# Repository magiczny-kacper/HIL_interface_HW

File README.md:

# HIL_interface_HW
Analog and digital I/O shield for Nucleo-144 board, designed for HIL simulation

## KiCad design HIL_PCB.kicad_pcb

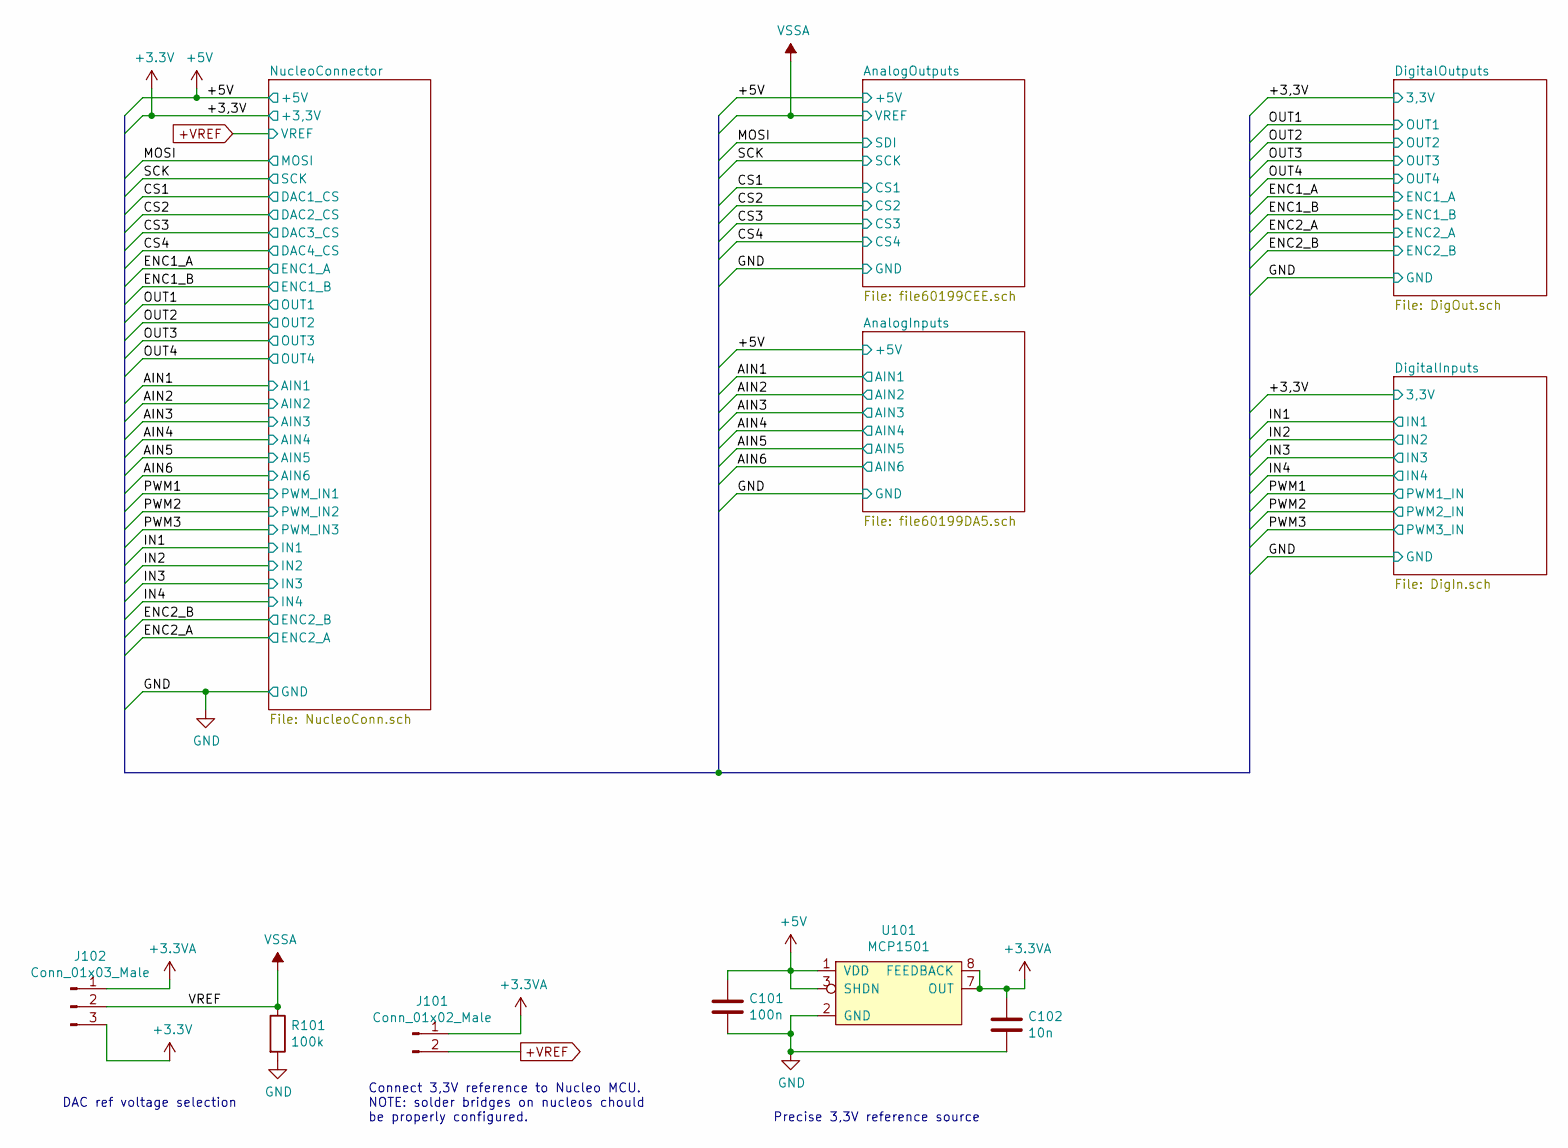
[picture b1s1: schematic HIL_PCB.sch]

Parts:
C101: 100n; C_0805_2012Metric
C102: 10n; C_0805_2012Metric
J101: Conn_01x02_Male; PinHeader_1x02_P2.54mm_Vertical
J102: Conn_01x03_Male; PinHeader_1x03_P2.54mm_Vertical
R101: 100k; R_0805_2012Metric
U101: MCP1501; SOIC-8_3.9x4.9mm_P1.27mm

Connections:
+3.3VA: C102.1, J101.1, J102.1, U101.7 (OUT), U101.8 (FEEDBACK)
+3V3: J102.3; also elsewhere on the board
+5V: C101.1, U101.1 (VDD), U101.3 (SHDN); also elsewhere on the board
+VREF: J101.2; also elsewhere on the board
GND: C101.2, C102.2, R101.2, U101.2 (GND), U101.4 (GND), U101.5 (GND), U101.6 (GND); also elsewhere on the board
VSSA: J102.2, R101.1; also elsewhere on the board

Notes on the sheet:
Connect 3,3V reference to Nucleo MCU. NOTE: solder bridges on nucleos chould be properly configured.
DAC ref voltage selection
Precise 3,3V reference source

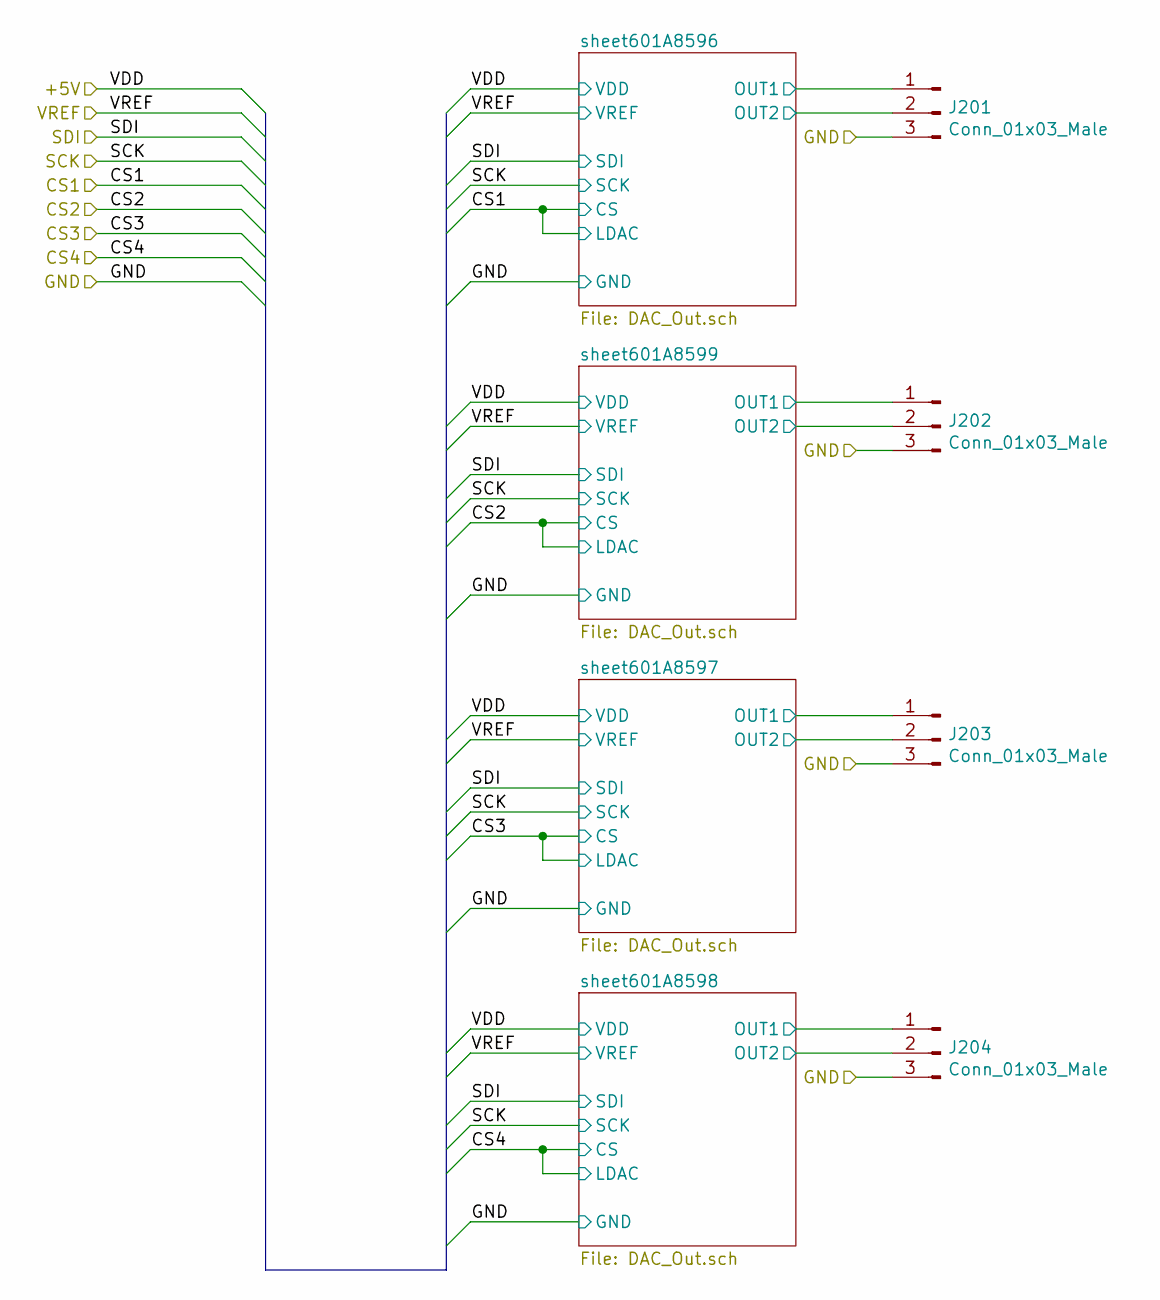
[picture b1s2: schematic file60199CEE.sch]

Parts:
J201, J202, J203, J204: Conn_01x03_Male; PinHeader_1x03_P2.54mm_Vertical

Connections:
/AnalogOutputs/sheet601A8596/OUT1: J201.1; also elsewhere on the board
/AnalogOutputs/sheet601A8596/OUT2: J201.2; also elsewhere on the board
/AnalogOutputs/sheet601A8597/OUT1: J203.1; also elsewhere on the board
/AnalogOutputs/sheet601A8597/OUT2: J203.2; also elsewhere on the board
/AnalogOutputs/sheet601A8598/OUT1: J204.1; also elsewhere on the board
/AnalogOutputs/sheet601A8598/OUT2: J204.2; also elsewhere on the board
/AnalogOutputs/sheet601A8599/OUT1: J202.1; also elsewhere on the board
/AnalogOutputs/sheet601A8599/OUT2: J202.2; also elsewhere on the board
GND: J201.3, J202.3, J203.3, J204.3; also elsewhere on the board

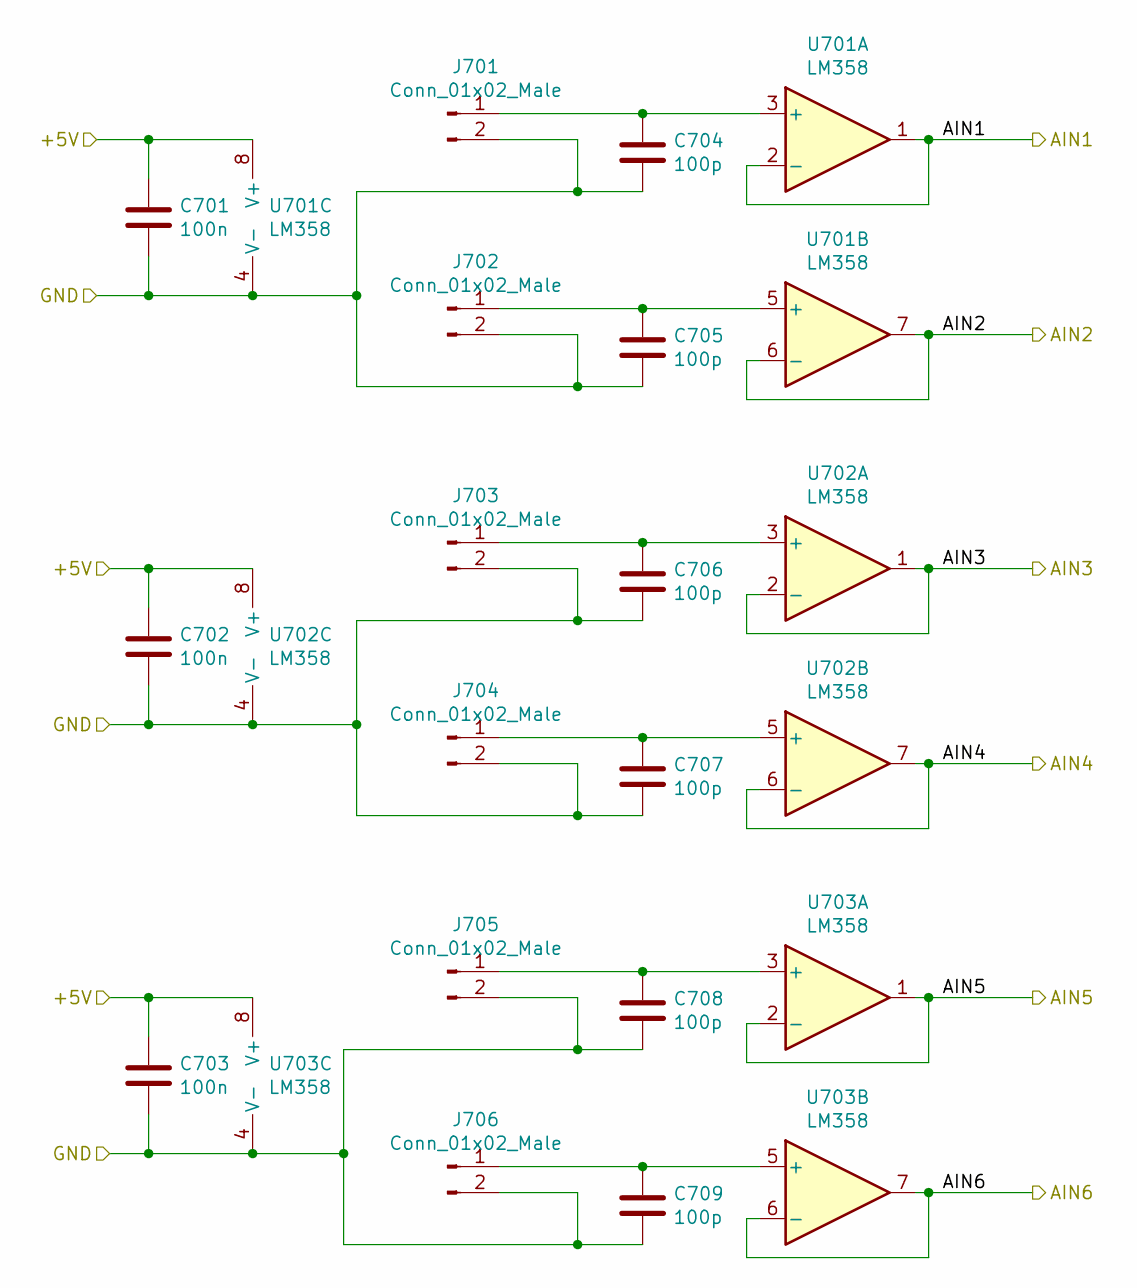
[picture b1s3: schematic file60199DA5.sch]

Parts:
C701, C702, C703: 100n; C_0805_2012Metric
C704, C705, C706, C707, C708, C709: 100p; C_0805_2012Metric
J701, J702, J703, J704, J705, J706: Conn_01x02_Male; PinHeader_1x02_P2.54mm_Vertical
U701, U702, U703: LM358; SO-8_3.9x4.9mm_P1.27mm

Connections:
+5V: C701.1, C702.1, C703.1, U701.8 (V+), U702.8 (V+), U703.8 (V+); also elsewhere on the board
/AIN1: U701.1, U701.2 (-); also elsewhere on the board
/AIN2: U701.6 (-), U701.7; also elsewhere on the board
/AIN3: U702.1, U702.2 (-); also elsewhere on the board
/AIN4: U702.6 (-), U702.7; also elsewhere on the board
/AIN5: U703.1, U703.2 (-); also elsewhere on the board
/AIN6: U703.6 (-), U703.7; also elsewhere on the board
GND: C701.2, C702.2, C703.2, C704.2, C705.2, C706.2, C707.2, C708.2, C709.2, J701.2, J702.2, J703.2, J704.2, J705.2, J706.2, U701.4 (V-), U702.4 (V-), U703.4 (V-); also elsewhere on the board
unnamed: C704.1, J701.1, U701.3 (+)
unnamed: C705.1, J702.1, U701.5 (+)
unnamed: C706.1, J703.1, U702.3 (+)
unnamed: C707.1, J704.1, U702.5 (+)
unnamed: C708.1, J705.1, U703.3 (+)
unnamed: C709.1, J706.1, U703.5 (+)

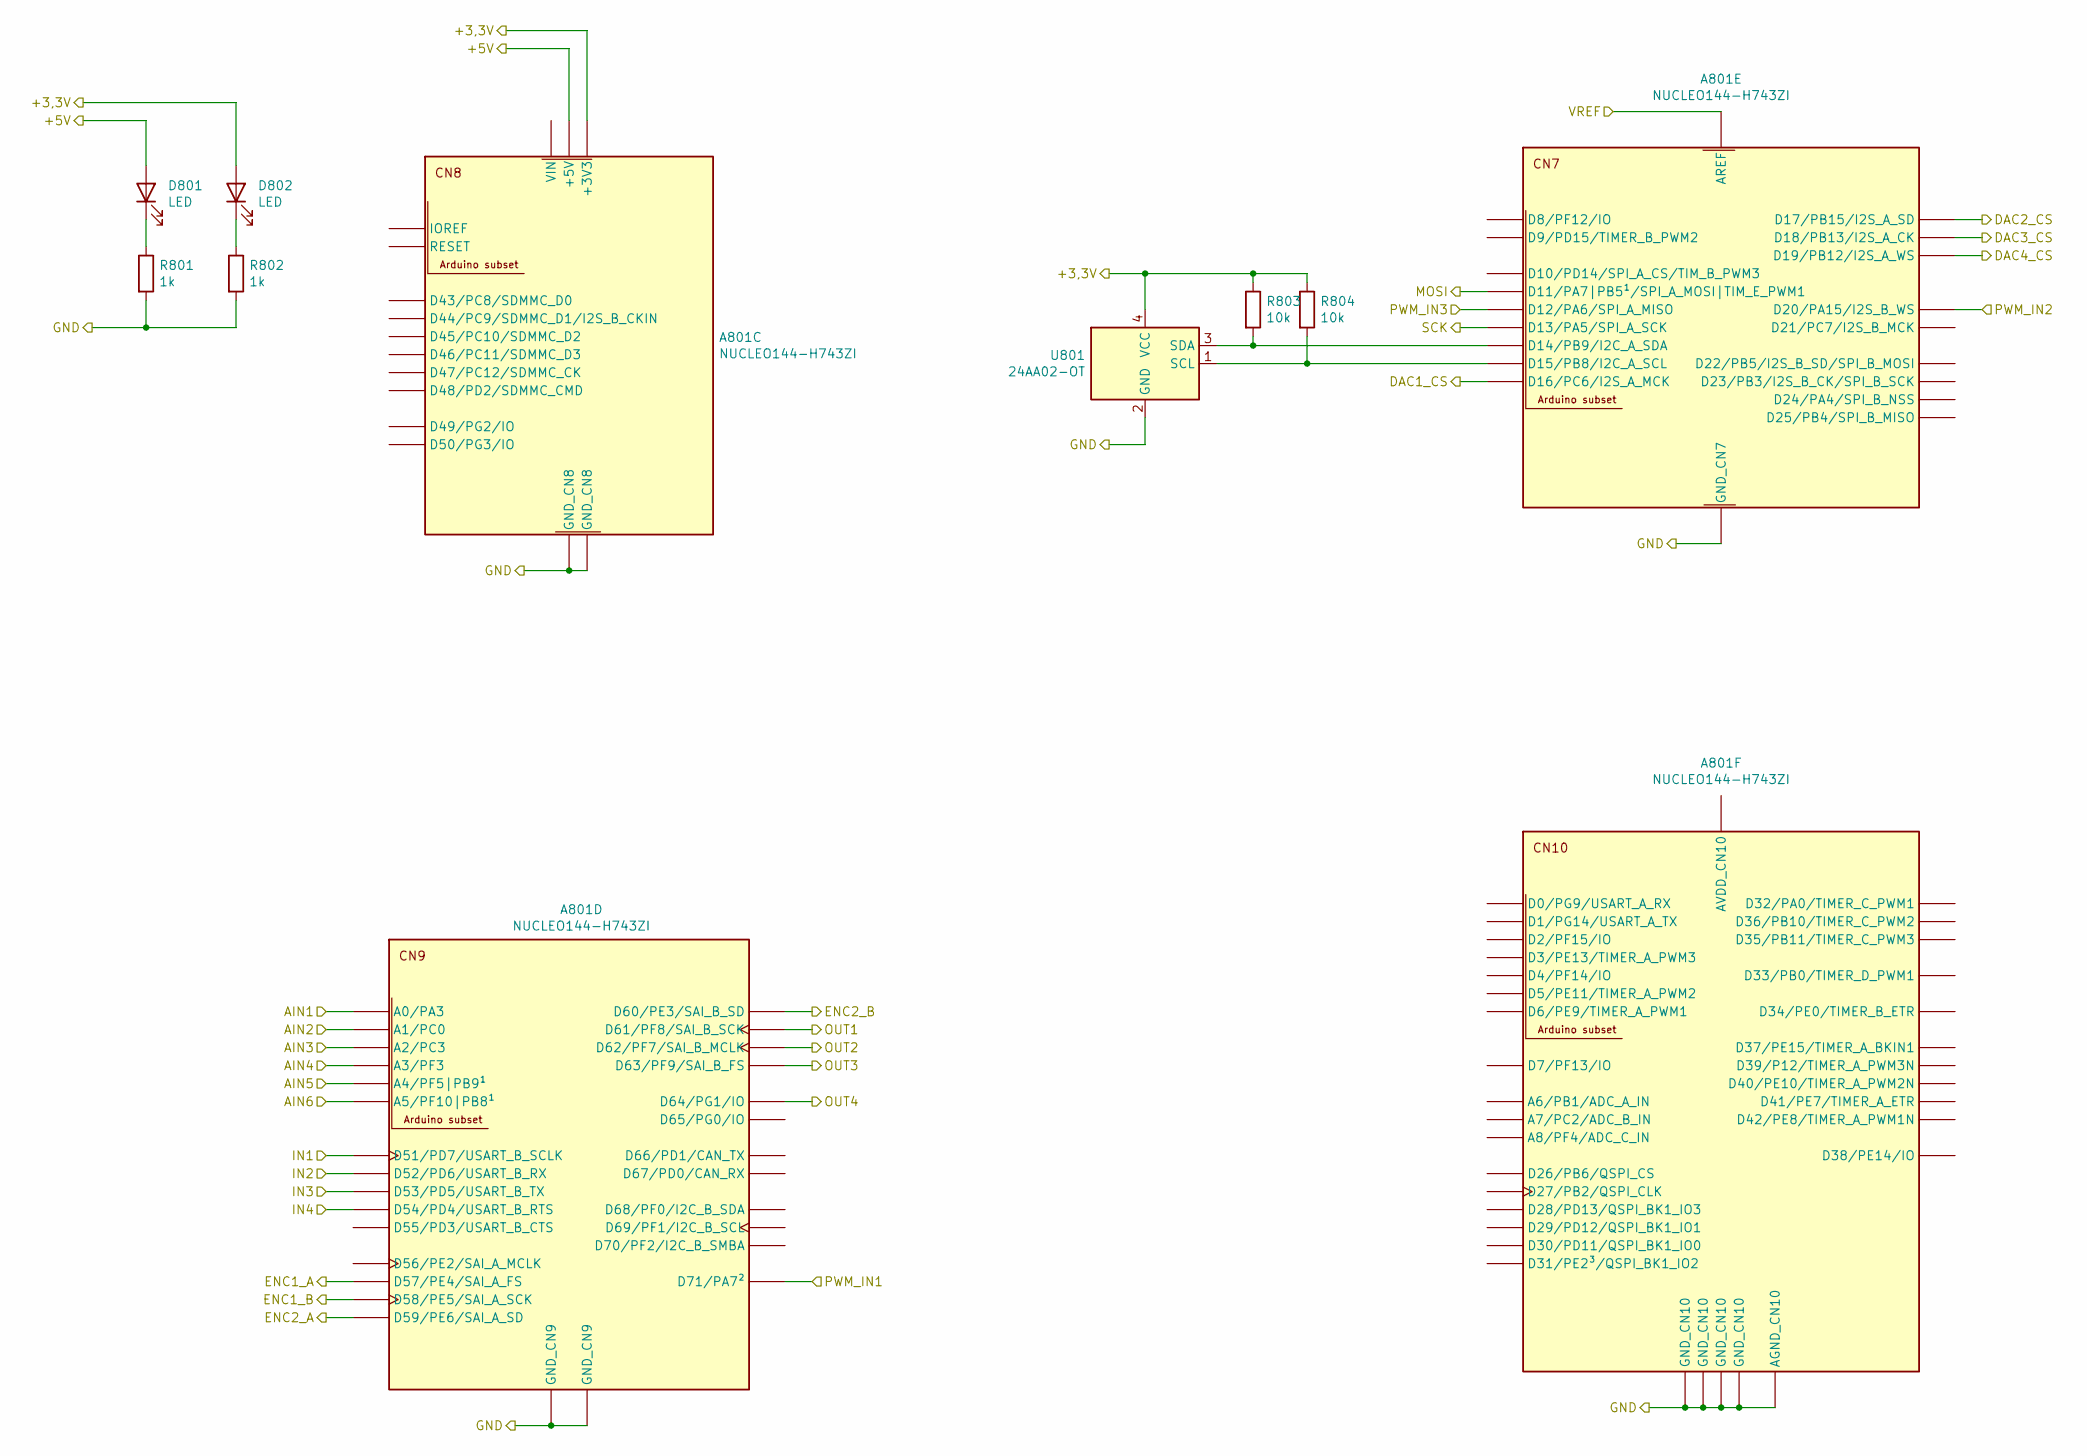
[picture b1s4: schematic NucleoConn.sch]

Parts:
A801: NUCLEO144-H743ZI; ST_Morpho_and_Zio_Connectors_144_STLink
D801, D802: LED; D_0805_2012Metric
R801, R802: 1k; R_0805_2012Metric
R803, R804: 10k; R_0805_2012Metric
U801: 24AA02-OT; SOT-23-5

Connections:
+3V3: A801.CN8_7 (+3V3), D802.2 (A), R803.1, R804.1, U801.4 (VCC); also elsewhere on the board
+5V: A801.CN8_9 (+5V), D801.2 (A); also elsewhere on the board
+VREF: A801.CN7_6 (AREF); also elsewhere on the board
/AIN1: A801.CN9_1 (A0/PA3); also elsewhere on the board
/AIN2: A801.CN9_3 (A1/PC0); also elsewhere on the board
/AIN3: A801.CN9_5 (A2/PC3); also elsewhere on the board
/AIN4: A801.CN9_7 (A3/PF3); also elsewhere on the board
/AIN5: A801.CN9_9 (A4/PF5|PB9¹); also elsewhere on the board
/AIN6: A801.CN9_11 (A5/PF10|PB8¹); also elsewhere on the board
/CS1: A801.CN7_1 (D16/PC6/I2S_A_MCK); also elsewhere on the board
/CS2: A801.CN7_3 (D17/PB15/I2S_A_SD); also elsewhere on the board
/CS3: A801.CN7_5 (D18/PB13/I2S_A_CK); also elsewhere on the board
/CS4: A801.CN7_7 (D19/PB12/I2S_A_WS); also elsewhere on the board
/ENC1_A: A801.CN9_16 (D57/PE4/SAI_A_FS); also elsewhere on the board
/ENC1_B: A801.CN9_18 (D58/PE5/SAI_A_SCK); also elsewhere on the board
/ENC2_A: A801.CN9_20 (D59/PE6/SAI_A_SD); also elsewhere on the board
/ENC2_B: A801.CN9_22 (D60/PE3/SAI_B_SD); also elsewhere on the board
/IN1: A801.CN9_2 (D51/PD7/USART_B_SCLK); also elsewhere on the board
/IN2: A801.CN9_4 (D52/PD6/USART_B_RX); also elsewhere on the board
/IN3: A801.CN9_6 (D53/PD5/USART_B_TX); also elsewhere on the board
/IN4: A801.CN9_8 (D54/PD4/USART_B_RTS); also elsewhere on the board
/MOSI: A801.CN7_14 (D11/PA7|PB5¹/SPI_A_MOSI|TIM_E_PWM1); also elsewhere on the board
/OUT1: A801.CN9_24 (D61/PF8/SAI_B_SCK); also elsewhere on the board
/OUT2: A801.CN9_26 (D62/PF7/SAI_B_MCLK); also elsewhere on the board
/OUT3: A801.CN9_28 (D63/PF9/SAI_B_FS); also elsewhere on the board
/OUT4: A801.CN9_30 (D64/PG1/IO); also elsewhere on the board
/PWM1: A801.CN9_15 (D71/PA7²); also elsewhere on the board
/PWM2: A801.CN7_9 (D20/PA15/I2S_B_WS); also elsewhere on the board
/PWM3: A801.CN7_12 (D12/PA6/SPI_A_MISO); also elsewhere on the board
/SCK: A801.CN7_10 (D13/PA5/SPI_A_SCK); also elsewhere on the board
GND: A801.CN7_8 (GND_CN7), A801.CN8_11 (GND_CN8), A801.CN8_13 (GND_CN8), A801.CN9_12 (GND_CN9), A801.CN9_23 (GND_CN9), A801.CN10_3 (AGND_CN10), A801.CN10_5 (GND_CN10), A801.CN10_17 (GND_CN10), A801.CN10_22 (GND_CN10), A801.CN10_27 (GND_CN10), R801.2, R802.2, U801.2 (GND); also elsewhere on the board
unnamed: A801.CN7_2 (D15/PB8/I2C_A_SCL), R804.2, U801.1 (SCL)
unnamed: A801.CN7_4 (D14/PB9/I2C_A_SDA), R803.2, U801.3 (SDA)
unnamed: D801.1 (K), R801.1
unnamed: D802.1 (K), R802.1

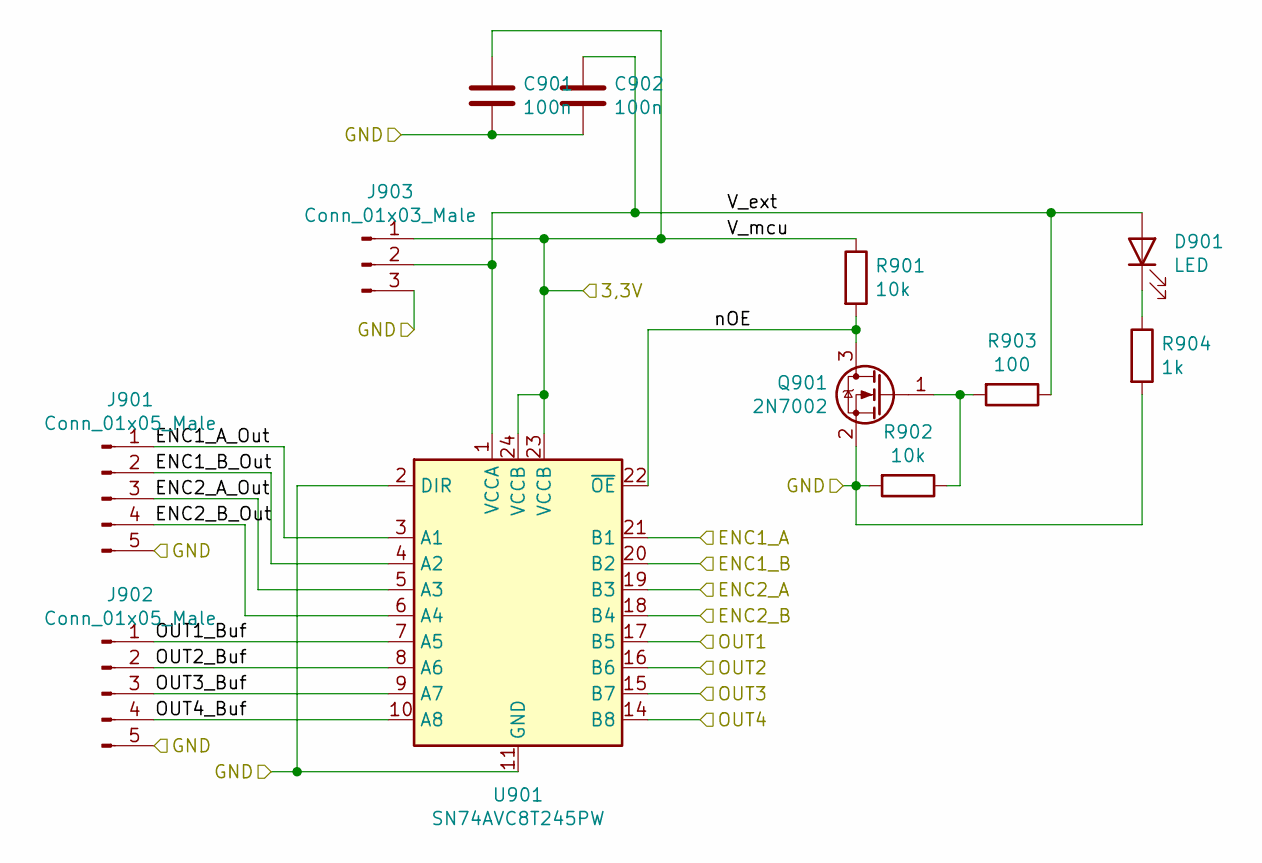
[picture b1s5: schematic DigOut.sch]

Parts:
C901, C902: 100n; C_0805_2012Metric
D901: LED; D_0805_2012Metric
J901, J902: Conn_01x05_Male; PinHeader_1x05_P2.54mm_Vertical
J903: Conn_01x03_Male; PinHeader_1x03_P2.54mm_Vertical
Q901: 2N7002; SOT-23
R901, R902: 10k; R_0805_2012Metric
R903: 100; R_0805_2012Metric
R904: 1k; R_0805_2012Metric
U901: SN74AVC8T245PW; TSSOP-24_4.4x7.8mm_P0.65mm

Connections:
+3V3: C901.1, J903.1, R901.1, U901.23 (VCCB), U901.24 (VCCB); also elsewhere on the board
/DigitalOutputs/ENC1_A_Out: J901.1, U901.3 (A1)
/DigitalOutputs/ENC1_B_Out: J901.2, U901.4 (A2)
/DigitalOutputs/ENC2_A_Out: J901.3, U901.5 (A3)
/DigitalOutputs/ENC2_B_Out: J901.4, U901.6 (A4)
/DigitalOutputs/OUT1_Buf: J902.1, U901.7 (A5)
/DigitalOutputs/OUT2_Buf: J902.2, U901.8 (A6)
/DigitalOutputs/OUT3_Buf: J902.3, U901.9 (A7)
/DigitalOutputs/OUT4_Buf: J902.4, U901.10 (A8)
/DigitalOutputs/V_ext: C902.1, D901.2 (A), J903.2, R903.1, U901.1 (VCCA)
/DigitalOutputs/nOE: Q901.3 (D), R901.2, U901.22 (~OE)
/ENC1_A: U901.21 (B1); also elsewhere on the board
/ENC1_B: U901.20 (B2); also elsewhere on the board
/ENC2_A: U901.19 (B3); also elsewhere on the board
/ENC2_B: U901.18 (B4); also elsewhere on the board
/OUT1: U901.17 (B5); also elsewhere on the board
/OUT2: U901.16 (B6); also elsewhere on the board
/OUT3: U901.15 (B7); also elsewhere on the board
/OUT4: U901.14 (B8); also elsewhere on the board
GND: C901.2, C902.2, J901.5, J902.5, J903.3, Q901.2 (S), R902.2, R904.2, U901.2 (DIR), U901.11 (GND), U901.12 (GND), U901.13 (GND); also elsewhere on the board
unnamed: D901.1 (K), R904.1
unnamed: Q901.1 (G), R902.1, R903.2

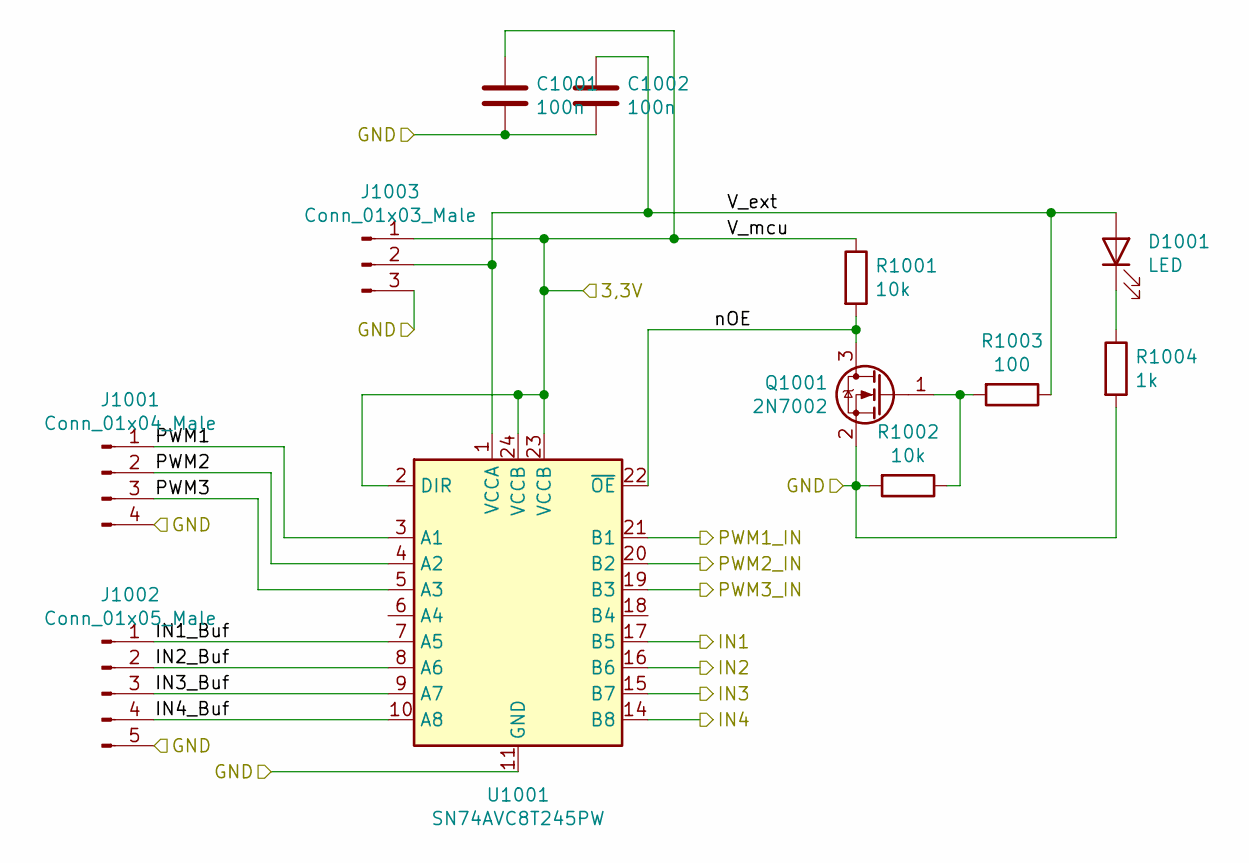
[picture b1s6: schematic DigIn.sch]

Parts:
C1001, C1002: 100n; C_0805_2012Metric
D1001: LED; D_0805_2012Metric
J1001: Conn_01x04_Male; PinHeader_1x04_P2.54mm_Vertical
J1002: Conn_01x05_Male; PinHeader_1x05_P2.54mm_Vertical
J1003: Conn_01x03_Male; PinHeader_1x03_P2.54mm_Vertical
Q1001: 2N7002; SOT-23
R1001, R1002: 10k; R_0805_2012Metric
R1003: 100; R_0805_2012Metric
R1004: 1k; R_0805_2012Metric
U1001: SN74AVC8T245PW; TSSOP-24_4.4x7.8mm_P0.65mm

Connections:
+3V3: C1001.1, J1003.1, R1001.1, U1001.2 (DIR), U1001.23 (VCCB), U1001.24 (VCCB); also elsewhere on the board
/DigitalInputs/IN1_Buf: J1002.1, U1001.7 (A5)
/DigitalInputs/IN2_Buf: J1002.2, U1001.8 (A6)
/DigitalInputs/IN3_Buf: J1002.3, U1001.9 (A7)
/DigitalInputs/IN4_Buf: J1002.4, U1001.10 (A8)
/DigitalInputs/PWM1: J1001.1, U1001.3 (A1)
/DigitalInputs/PWM2: J1001.2, U1001.4 (A2)
/DigitalInputs/PWM3: J1001.3, U1001.5 (A3)
/DigitalInputs/V_ext: C1002.1, D1001.2 (A), J1003.2, R1003.1, U1001.1 (VCCA)
/DigitalInputs/nOE: Q1001.3 (D), R1001.2, U1001.22 (~OE)
/IN1: U1001.17 (B5); also elsewhere on the board
/IN2: U1001.16 (B6); also elsewhere on the board
/IN3: U1001.15 (B7); also elsewhere on the board
/IN4: U1001.14 (B8); also elsewhere on the board
/PWM1: U1001.21 (B1); also elsewhere on the board
/PWM2: U1001.20 (B2); also elsewhere on the board
/PWM3: U1001.19 (B3); also elsewhere on the board
GND: C1001.2, C1002.2, J1001.4, J1002.5, J1003.3, Q1001.2 (S), R1002.2, R1004.2, U1001.11 (GND), U1001.12 (GND), U1001.13 (GND); also elsewhere on the board
unnamed: D1001.1 (K), R1004.1
unnamed: Q1001.1 (G), R1002.1, R1003.2

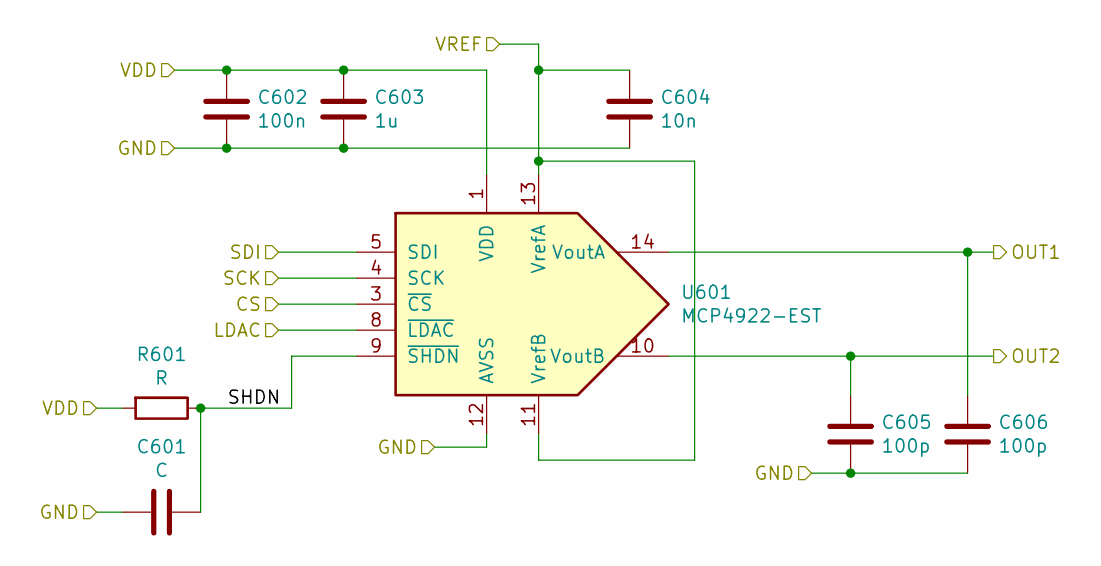
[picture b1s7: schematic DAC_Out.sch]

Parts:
C201: C; C_0805_2012Metric
C202: 100n; C_0805_2012Metric
C203: 1u; C_0805_2012Metric
C204: 10n; C_0805_2012Metric
C205, C206: 100p; C_0805_2012Metric
R201: R; R_0805_2012Metric
U201: MCP4922-EST; TSSOP-14_4.4x5mm_P0.65mm

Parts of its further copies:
C301, C401, C501, C601: C; C_0805_2012Metric
C302, C402, C502, C602: 100n; C_0805_2012Metric
C303, C403, C503, C603: 1u; C_0805_2012Metric
C304, C404, C504, C604: 10n; C_0805_2012Metric
C305, C306, C405, C406, C505, C506, C605, C606: 100p; C_0805_2012Metric
R301, R401, R501, R601: R; R_0805_2012Metric
U301, U401, U501, U601: MCP4922-EST; TSSOP-14_4.4x5mm_P0.65mm

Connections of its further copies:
+5V: C302.1, C303.1, C402.1, C403.1, C502.1, C503.1, C602.1, C603.1, R301.2, R401.2, R501.2, R601.2, U301.1 (VDD), U401.1 (VDD), U501.1 (VDD), U601.1 (VDD); also elsewhere on the board
/AnalogOutputs/sheet601A8596/OUT1: C306.1, U301.14 (VoutA); also elsewhere on the board
/AnalogOutputs/sheet601A8596/OUT2: C305.1, U301.10 (VoutB); also elsewhere on the board
/AnalogOutputs/sheet601A8596/SHDN: C301.1, R301.1, U301.9 (~SHDN~)
/AnalogOutputs/sheet601A8597/OUT1: C406.1, U401.14 (VoutA); also elsewhere on the board
/AnalogOutputs/sheet601A8597/OUT2: C405.1, U401.10 (VoutB); also elsewhere on the board
/AnalogOutputs/sheet601A8597/SHDN: C401.1, R401.1, U401.9 (~SHDN~)
/AnalogOutputs/sheet601A8598/OUT1: C506.1, U501.14 (VoutA); also elsewhere on the board
/AnalogOutputs/sheet601A8598/OUT2: C505.1, U501.10 (VoutB); also elsewhere on the board
/AnalogOutputs/sheet601A8598/SHDN: C501.1, R501.1, U501.9 (~SHDN~)
/AnalogOutputs/sheet601A8599/OUT1: C606.1, U601.14 (VoutA); also elsewhere on the board
/AnalogOutputs/sheet601A8599/OUT2: C605.1, U601.10 (VoutB); also elsewhere on the board
/AnalogOutputs/sheet601A8599/SHDN: C601.1, R601.1, U601.9 (~SHDN~)
/CS1: U301.3 (~CS~), U301.8 (~LDAC~); also elsewhere on the board
/CS2: U601.3 (~CS~), U601.8 (~LDAC~); also elsewhere on the board
/CS3: U401.3 (~CS~), U401.8 (~LDAC~); also elsewhere on the board
/CS4: U501.3 (~CS~), U501.8 (~LDAC~); also elsewhere on the board
/MOSI: U301.5 (SDI), U401.5 (SDI), U501.5 (SDI), U601.5 (SDI); also elsewhere on the board
/SCK: U301.4 (SCK), U401.4 (SCK), U501.4 (SCK), U601.4 (SCK); also elsewhere on the board
GND: C301.2, C302.2, C303.2, C304.2, C305.2, C306.2, C401.2, C402.2, C403.2, C404.2, C405.2, C406.2, C501.2, C502.2, C503.2, C504.2, C505.2, C506.2, C601.2, C602.2, C603.2, C604.2, C605.2, C606.2, U301.12 (AVSS), U401.12 (AVSS), U501.12 (AVSS), U601.12 (AVSS); also elsewhere on the board
VSSA: C304.1, C404.1, C504.1, C604.1, U301.11 (VrefB), U301.13 (VrefA), U401.11 (VrefB), U401.13 (VrefA), U501.11 (VrefB), U501.13 (VrefA), U601.11 (VrefB), U601.13 (VrefA); also elsewhere on the board

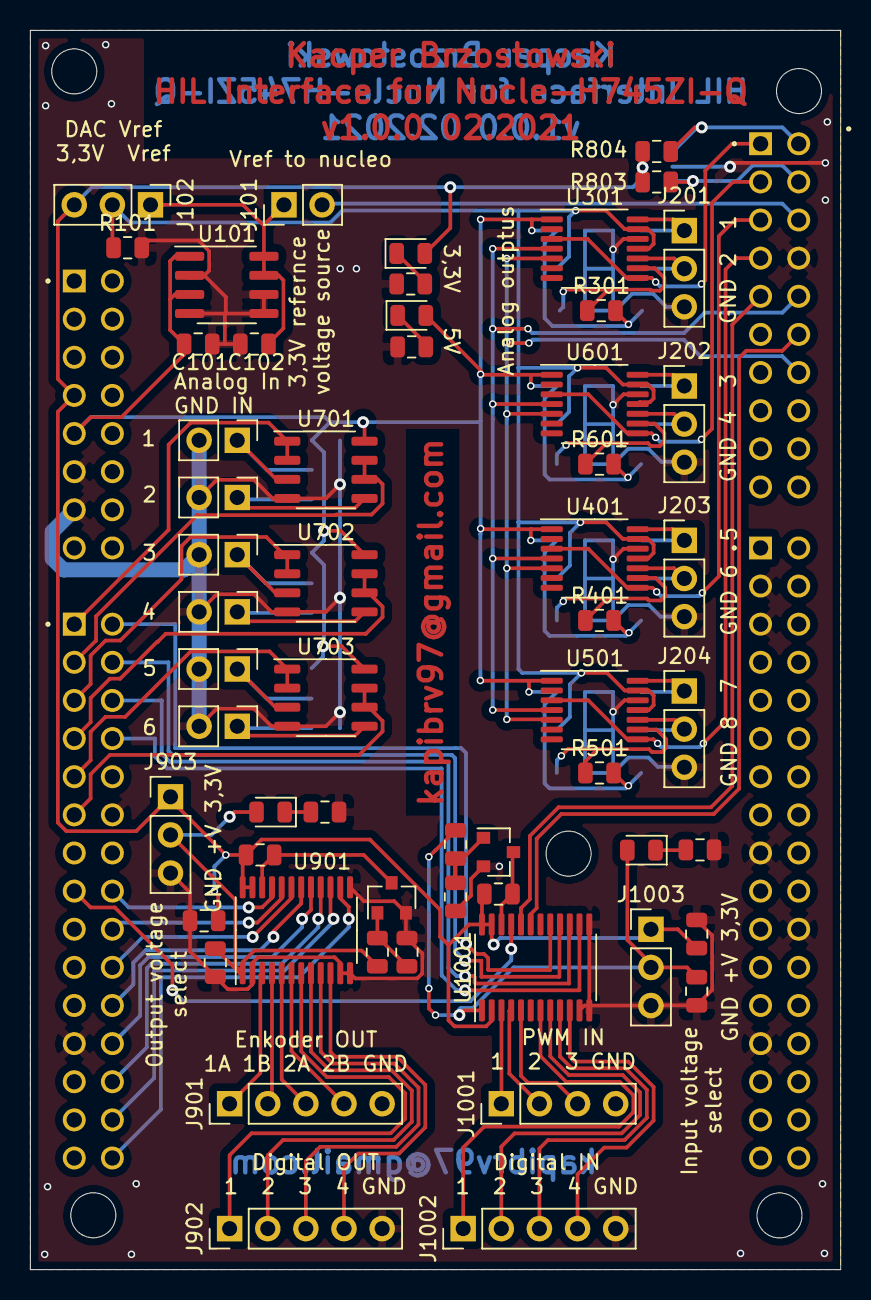
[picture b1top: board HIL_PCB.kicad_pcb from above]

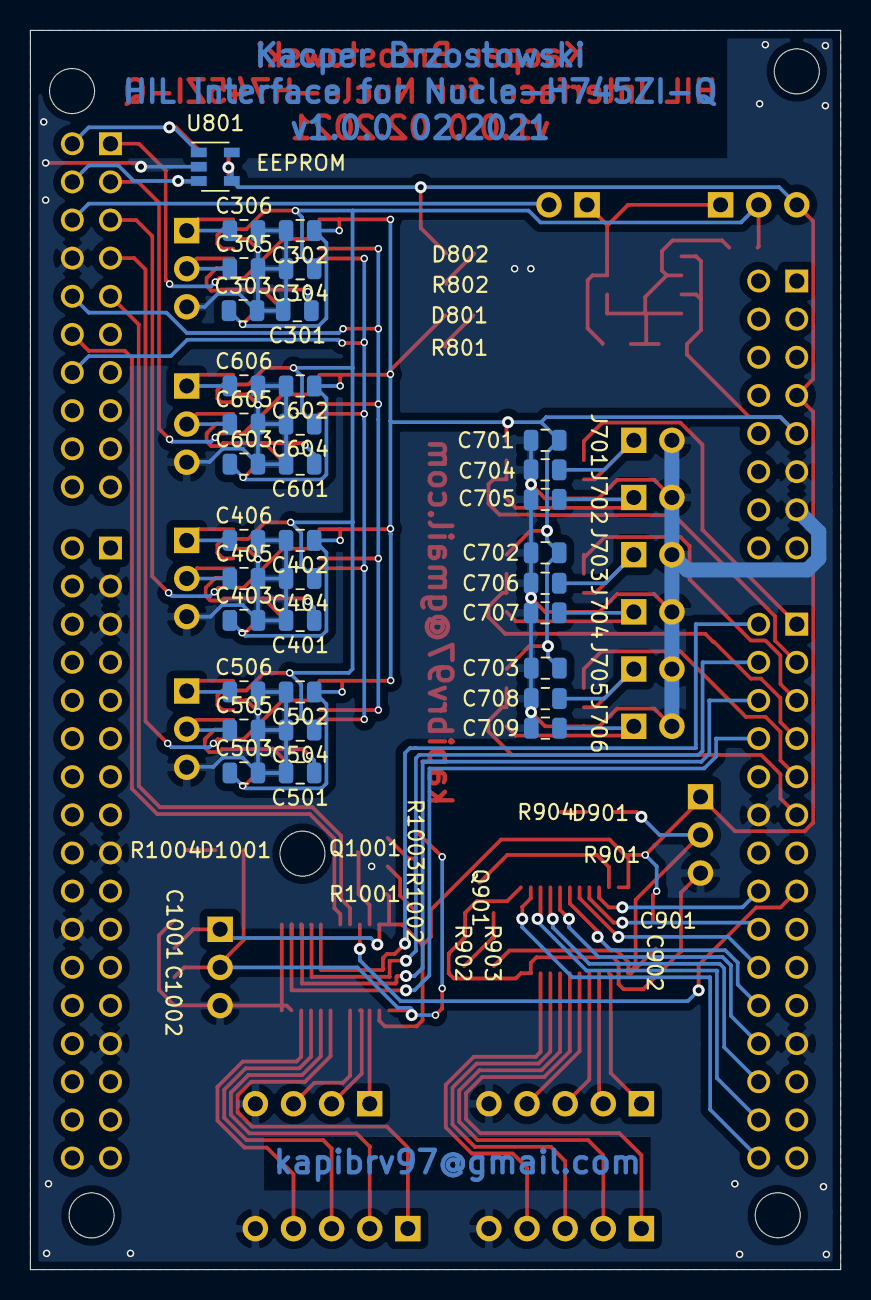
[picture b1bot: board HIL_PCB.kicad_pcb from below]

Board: 2 copper layers, 54.0 x 82.5 mm, 92 parts (34 on the bottom side), 78 nets.

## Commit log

2021-02-22 First version of pcb
